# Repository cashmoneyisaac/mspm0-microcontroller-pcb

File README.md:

# mspm0 microcontroller pcb

my first custom microcontroller board, built around the ti mspm0g3507 in kicad 9. i made this project to learn pcb design, component selection, and how to take a schematic through layout and manufacturing preparation.

## hardware

- ti mspm0g3507 microcontroller with an external 8 mhz crystal
- usb-c power input with usb data-line esd protection
- spx3819 3.3 v regulator
- ch340e usb-to-uart bridge
- lis2dh three-axis accelerometer connected over i²c
- tag-connect swd programming and debug access
- two-layer pcb with ground pours and 32 fitted components

## files

- editable kicad project, schematic, board, and symbol libraries in the root folder
- [schematic pdf](docs/Reviewed-schematic.pdf)
- [board layout](docs/Reviewed-board.svg)
- [design review](docs/Final-review.md)
- [gerbers and drill files](manufacturing/gerbers/)
- [bom, placement files, and assembly notes](manufacturing/assembly/README.md)

isaac nuriddin · electrical engineering · embry-riddle aeronautical university

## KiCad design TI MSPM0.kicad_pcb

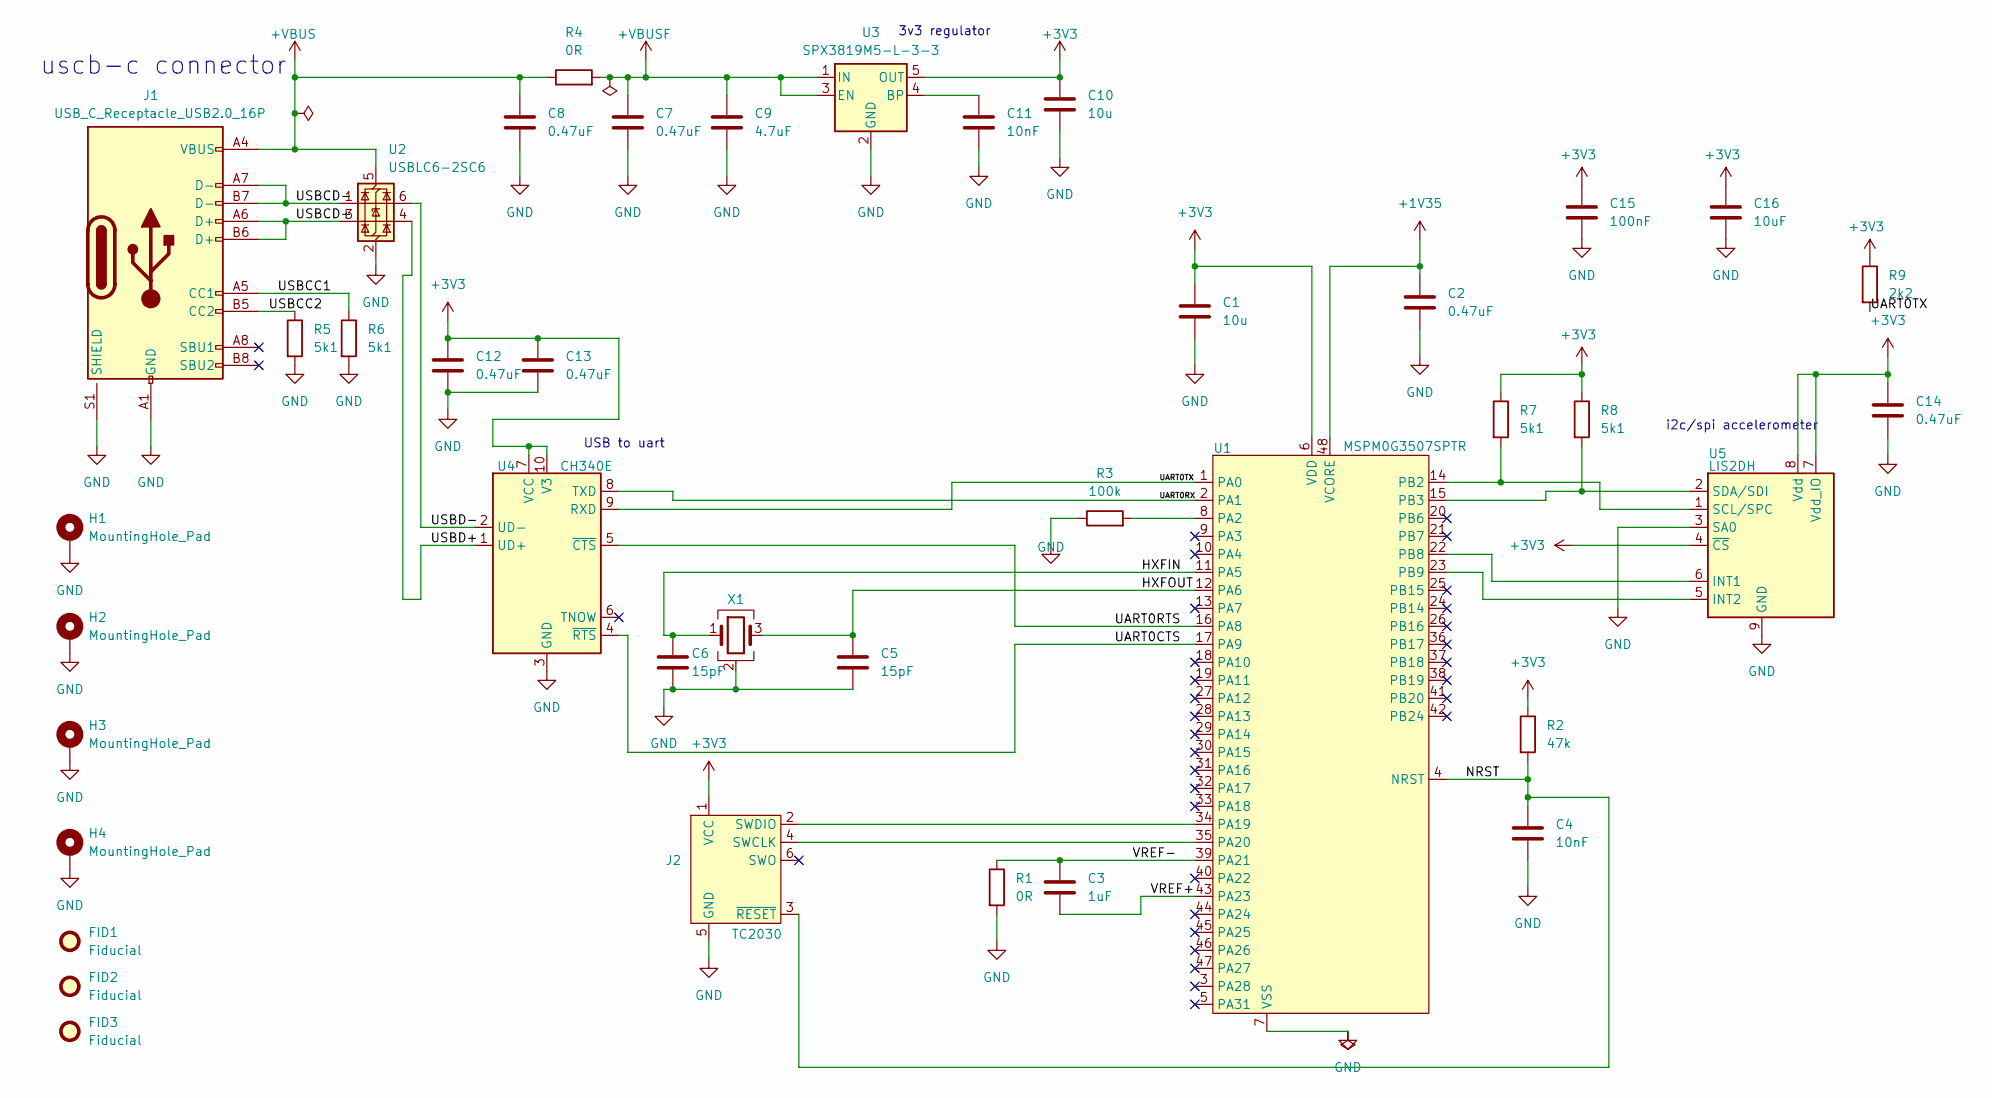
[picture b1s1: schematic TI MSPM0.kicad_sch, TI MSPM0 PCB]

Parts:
C1, C10: 10u; C_1206_3216Metric; Tolerance ±10%; Voltage 25V; MPN CL31A106KAHNNN
C2, C7, C8, C12, C13, C14: 0.47uF; C_0603_1608Metric; Tolerance ±10%; Digikey PN 490-3295-1-ND
C3: 1uF; C_0603_1608Metric; Tolerance ±10%
C4, C11: 10nF; C_0603_1608Metric; Tolerance ±10%
C5, C6: 15pF; C_0603_1608Metric; Tolerance ±10%
C9: 4.7uF; C_1206_3216Metric; Tolerance ±10%; Voltage 25V
C15: 100nF; C_0603_1608Metric
C16: 10uF; C_1206_3216Metric
FID1, FID2, FID3: Fiducial; Fiducial_1mm_Mask2mm
H1, H2, H3, H4: MountingHole_Pad; MountingHole_2.2mm_M2_Pad
J1: USB_C_Receptacle_USB2.0_16P; USB_C_Receptacle_GCT_USB4105-xx-A_16P_TopMnt_Horizontal
J2: TC2030; Tag-Connect_TC2030-IDC-FP_2x03_P1.27mm_Vertical
R1, R4: 0R; R_0603_1608Metric
R2: 47k; R_0603_1608Metric
R3: 100k; R_0603_1608Metric; PartNumber AT0603BRD07100KL; JLCPCBPart# C855559
R5, R6, R7, R8: 5k1; R_0603_1608Metric
R9: 2k2; R_0603_1608Metric
U1: MSPM0G3507SPTR; LQFP-48_7x7mm_P0.5mm
U2: USBLC6-2SC6; SOT-23-6
U3: SPX3819M5-L-3-3; SOT-23-5
U4: CH340E; MSOP-10_3x3mm_P0.5mm
U5: LIS2DH; LGA-14_2x2mm_P0.35mm_LayoutBorder3x4y
X1: ECS-80-12-33-JGN-TR3; Crystal_SMD_3225-4Pin_3.2x2.5mm

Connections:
+1V35: C2.1, U1.48 (VCORE)
+3V3: C1.2, C10.2, C12.1, C13.1, C14.1, C15.1, C16.1, J2.1 (VCC), R2.1, R7.1, R8.1, R9.1, U1.6 (VDD), U3.5 (OUT), U4.7 (VCC), U4.10 (V3), U5.4 (~CS), U5.7 (Vdd_IO), U5.8 (Vdd)
+VBUS: C8.1, J1.A4 (VBUS), J1.A9 (VBUS), J1.B4 (VBUS), J1.B9 (VBUS), R4.1, U2.5 (VBUS)
+VBUSF: C7.1, C9.2, R4.2, U3.1 (IN), U3.3 (EN)
/HXFIN: C6.1, U1.11 (PA5), X1.1
/HXFOUT: C5.1, U1.12 (PA6), X1.3
/NRST: C4.1, J2.3 (~RESET), R2.2, U1.4 (NRST)
/UART0CTS: U1.17 (PA9), U4.4 (~RTS)
/UART0RTS: U1.16 (PA8), U4.5 (~CTS)
/UART0RX: U1.2 (PA1), U4.8 (TXD)
/UART0TX: R9.2, U1.1 (PA0), U4.9 (RXD)
/USBCC1: J1.A5 (CC1), R6.1
/USBCC2: J1.B5 (CC2), R5.1
/USBCD+: J1.A6 (D+), J1.B6 (D+), U2.3 (I/O2)
/USBCD-: J1.A7 (D-), J1.B7 (D-), U2.1 (I/O1)
/USBD+: U2.4 (I/O2), U4.1 (UD+)
/USBD-: U2.6 (I/O1), U4.2 (UD-)
/VREF+: C3.2, U1.43 (PA23)
/VREF-: C3.1, R1.1, U1.39 (PA21)
GND: C1.1, C2.2, C4.2, C5.2, C6.2, C7.2, C8.2, C9.1, C10.1, C11.2, C12.2, C13.2, C14.2, C15.2, C16.2, H1.1 (1_1), H2.1 (1_1), H3.1 (1_1), H4.1 (1_1), J1.A1 (GND), J1.A12 (GND), J1.B1 (GND), J1.B12 (GND), J1.S1 (SHIELD), J2.5 (GND), R1.2, R3.1, R5.2, R6.2, U1.7 (VSS), U2.2 (GND), U3.2 (GND), U4.3 (GND), U5.3 (SA0), U5.9 (GND), U5.10 (GND), U5.11 (GND), U5.12 (GND), U5.13 (GND), U5.14 (GND), X1.2 (G), X1.4 (G)
unnamed: J2.4 (SWCLK), U1.35 (PA20)
unnamed: J2.2 (SWDIO), U1.34 (PA19)
unnamed: R3.2, U1.8 (PA2)
unnamed: R7.2, U1.14 (PB2), U5.1 (SCL/SPC)
unnamed: R8.2, U1.15 (PB3), U5.2 (SDA/SDI)
unnamed: U1.22 (PB8), U5.6 (INT1)
unnamed: U1.23 (PB9), U5.5 (INT2)
unnamed: C11.1, U3.4 (BP)

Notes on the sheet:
i2c/spi accelerometer
uscb-c connector
USB to uart
3v3 regulator

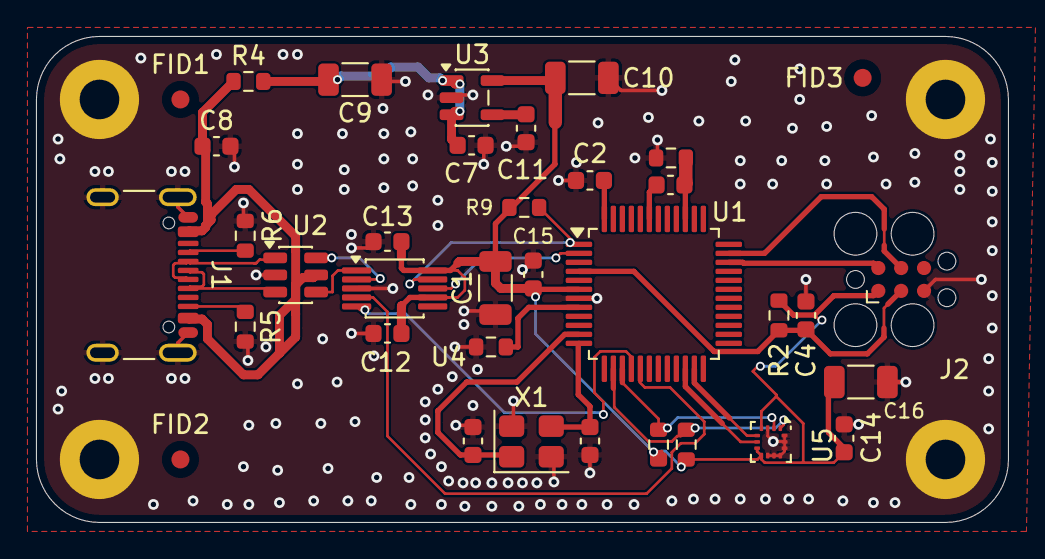
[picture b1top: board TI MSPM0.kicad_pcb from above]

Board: 2 copper layers, 54.0 x 27.0 mm, 40 parts (0 on the bottom side), 28 nets.
